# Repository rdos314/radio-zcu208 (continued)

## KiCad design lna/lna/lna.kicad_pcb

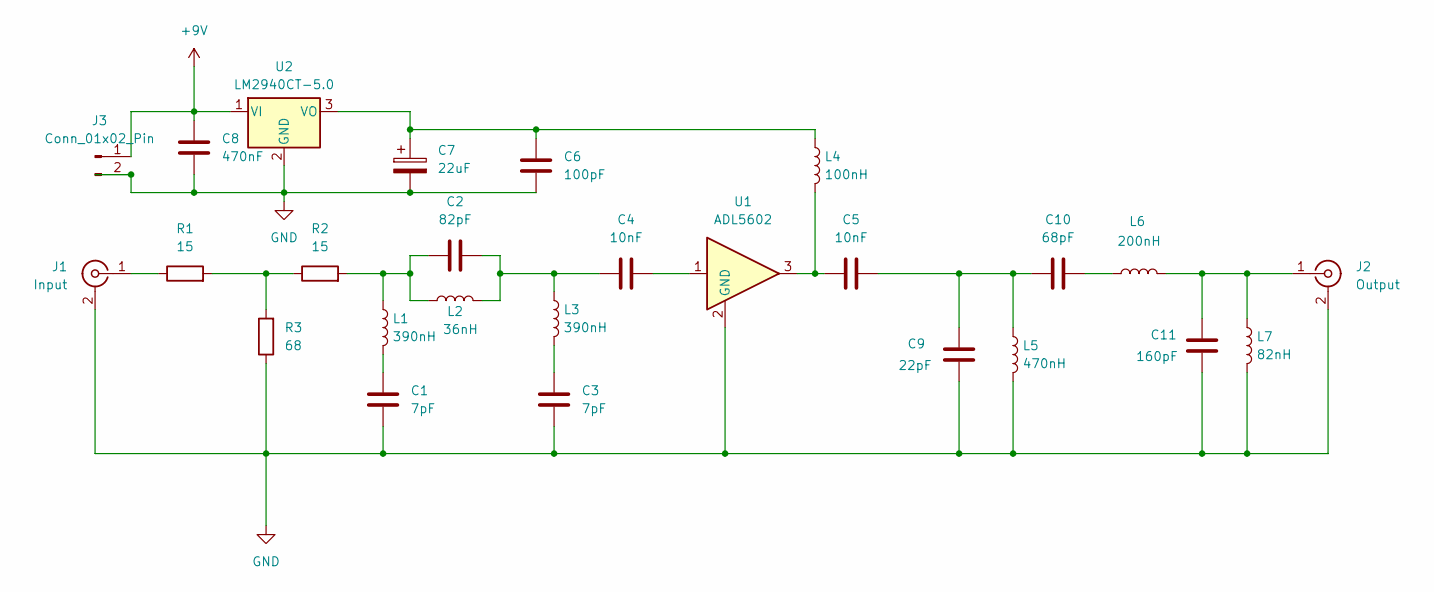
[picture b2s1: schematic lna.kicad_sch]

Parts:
C1, C3: 7pF; C_0402_1005Metric_Pad0.74x0.62mm_HandSolder
C2: 82pF; C_0402_1005Metric_Pad0.74x0.62mm_HandSolder
C4, C5: 10nF; C_0402_1005Metric_Pad0.74x0.62mm_HandSolder
C6: 100pF; C_0805_2012Metric_Pad1.18x1.45mm_HandSolder
C7: 22uF; CP_Radial_D6.3mm_P2.50mm
C8: 470nF; C_Radial_D10.0mm_H12.5mm_P5.00mm
C9: 22pF; C_0402_1005Metric_Pad0.74x0.62mm_HandSolder
C10: 68pF; C_0402_1005Metric_Pad0.74x0.62mm_HandSolder
C11: 160pF; C_0402_1005Metric_Pad0.74x0.62mm_HandSolder
J1: Input; SMA_Amphenol_132289_EdgeMount
J2: Output; SMA_Amphenol_132289_EdgeMount
J3: Conn_01x02_Pin; PinHeader_1x02_P2.54mm_Vertical
L1, L3: 390nH; L_0402_1005Metric_Pad0.77x0.64mm_HandSolder
L2: 36nH; L_0402_1005Metric_Pad0.77x0.64mm_HandSolder
L4: 100nH; L_0805_2012Metric_Pad1.05x1.20mm_HandSolder
L5: 470nH; L_0402_1005Metric_Pad0.77x0.64mm_HandSolder
L6: 200nH; L_0402_1005Metric_Pad0.77x0.64mm_HandSolder
L7: 82nH; L_0402_1005Metric_Pad0.77x0.64mm_HandSolder
R1, R2: 15; R_0402_1005Metric_Pad0.72x0.64mm_HandSolder
R3: 68; R_0402_1005Metric_Pad0.72x0.64mm_HandSolder
U1: ADL5602; SOT-89-3_Handsoldering
U2: LM2940CT-5.0; TO-220-3_Horizontal_TabDown

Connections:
+9V: C8.1, J3.1, U2.1 (VI)
GND: C1.2, C3.2, C6.2, C7.2, C8.2, C9.2, C11.2, J1.2 (Ext), J2.2 (Ext), J3.2, L5.2, L7.2, R3.1, U1.2 (GND_2), U2.2 (GND)
unnamed: C1.1, L1.2
unnamed: C2.1, L1.1, L2.1, R2.2
unnamed: C2.2, C4.1, L2.2, L3.1
unnamed: C3.1, L3.2
unnamed: C4.2, U1.1
unnamed: C5.1, L4.2, U1.3
unnamed: C5.2, C9.1, C10.1, L5.1
unnamed: C10.2, L6.1
unnamed: J1.1 (In), R1.1
unnamed: C11.1, J2.1 (In), L6.2, L7.1
unnamed: R1.2, R2.1, R3.2
unnamed: C6.1, C7.1, L4.1, U2.3 (VO)

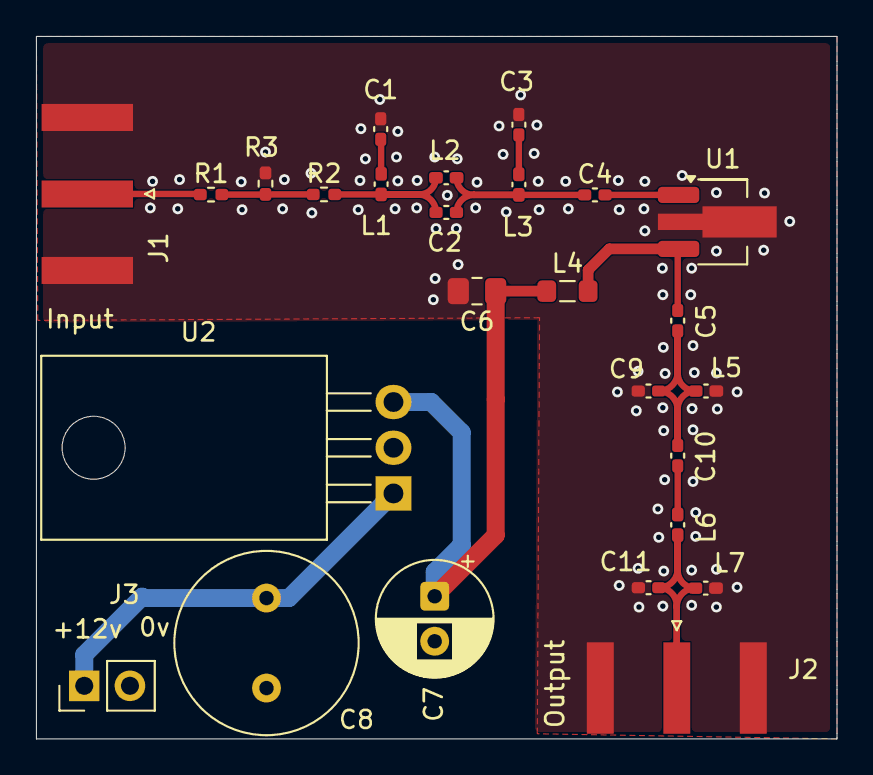
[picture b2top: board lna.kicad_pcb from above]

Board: 4 copper layers, 44.5 x 39.0 mm, 26 parts (0 on the bottom side), 14 nets.

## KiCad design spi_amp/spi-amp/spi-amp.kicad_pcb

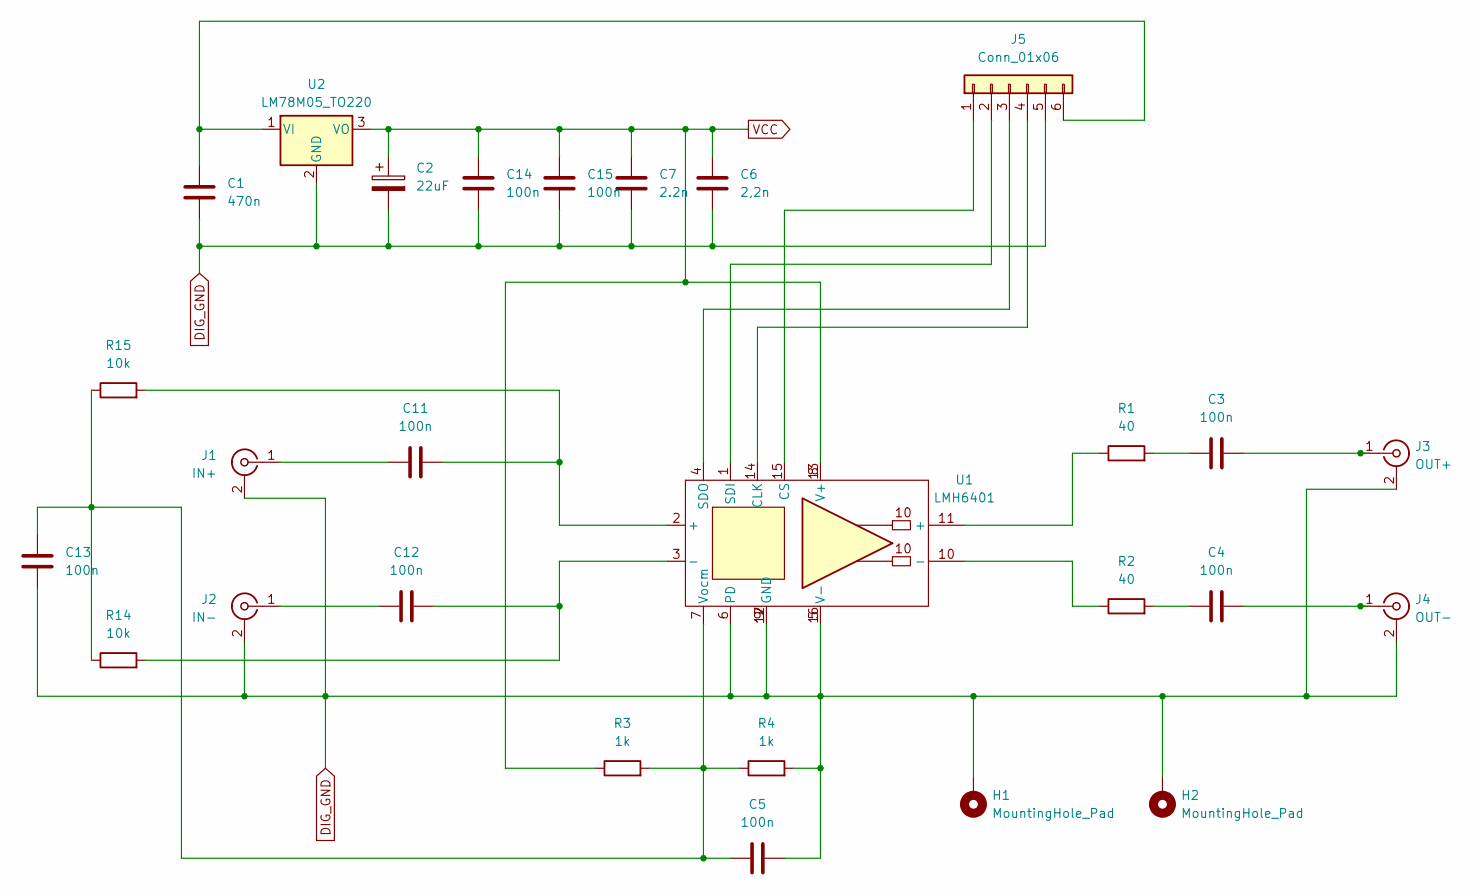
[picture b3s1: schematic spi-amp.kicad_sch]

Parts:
C1: 470n; C_Disc_D4.3mm_W1.9mm_P5.00mm
C2: 22uF; CP_Radial_D6.3mm_P2.50mm
C3, C4, C11, C12: 100n; C_0402_1005Metric_Pad0.74x0.62mm_HandSolder
C5, C13, C14, C15: 100n; C_0805_2012Metric_Pad1.18x1.45mm_HandSolder
C6: 2,2n; C_0402_1005Metric_Pad0.74x0.62mm_HandSolder
C7: 2.2n; C_0402_1005Metric_Pad0.74x0.62mm_HandSolder
H1, H2: MountingHole_Pad; MountingHole_3.2mm_M3_Pad
J1: IN+; SMA_Amphenol_132289_EdgeMount
J2: IN-; SMA_Amphenol_132289_EdgeMount
J3: OUT+; SMA_Amphenol_132289_EdgeMount
J4: OUT-; SMA_Amphenol_132289_EdgeMount
J5: Conn_01x06; PinSocket_1x06_P2.54mm_Horizontal
R1, R2: 40; R_0402_1005Metric_Pad0.72x0.64mm_HandSolder
R3, R4: 1k; R_0805_2012Metric_Pad1.20x1.40mm_HandSolder
R14, R15: 10k; R_0402_1005Metric_Pad0.72x0.64mm_HandSolder
U1: LMH6401; UQFN-16-custom
U2: LM78M05_TO220; TO-220-3_Horizontal_TabDown

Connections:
DIG_GND: C1.2, C2.2, C5.2, C6.1, C7.1, C13.1, C14.1, C15.1, H1.1 (1_1), H2.1 (1_1), J1.2 (Ext), J2.2 (Ext), J3.2 (Ext), J4.2 (Ext), J5.5, R4.2, U1.5 (V-), U1.6 (PD), U1.9 (GND), U1.12 (GND), U1.16 (V-), U1.17 (GND), U2.2 (GND)
unnamed: C3.1, R1.2
unnamed: C4.1, R2.2
unnamed: C11.2, R15.2, U1.2 (+)
unnamed: C12.2, R14.2, U1.3 (-)
unnamed: C11.1, J1.1 (In)
unnamed: C12.1, J2.1 (In)
unnamed: C3.2, J3.1 (In)
unnamed: C4.2, J4.1 (In)
unnamed: J5.1, U1.15 (CS)
unnamed: J5.2, U1.1 (SDI)
unnamed: J5.3, U1.4 (SDO)
unnamed: J5.4, U1.14 (CLK)
unnamed: C1.1, J5.6, U2.1 (VI)
unnamed: R1.1, U1.11 (+)
unnamed: R2.1, U1.10 (-)
unnamed: C5.1, C13.2, R3.2, R4.1, R14.1, R15.1, U1.7 (Vocm)
VCC: C2.1, C6.2, C7.2, C14.2, C15.2, R3.1, U1.8 (V+), U1.13 (V+), U2.3 (VO)

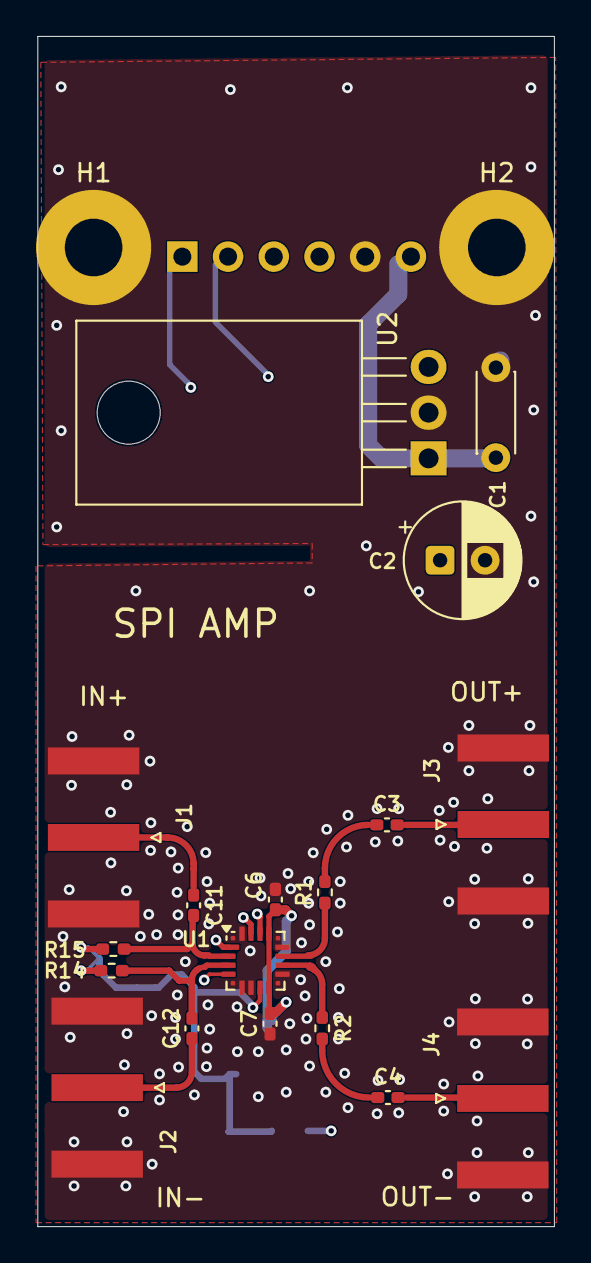
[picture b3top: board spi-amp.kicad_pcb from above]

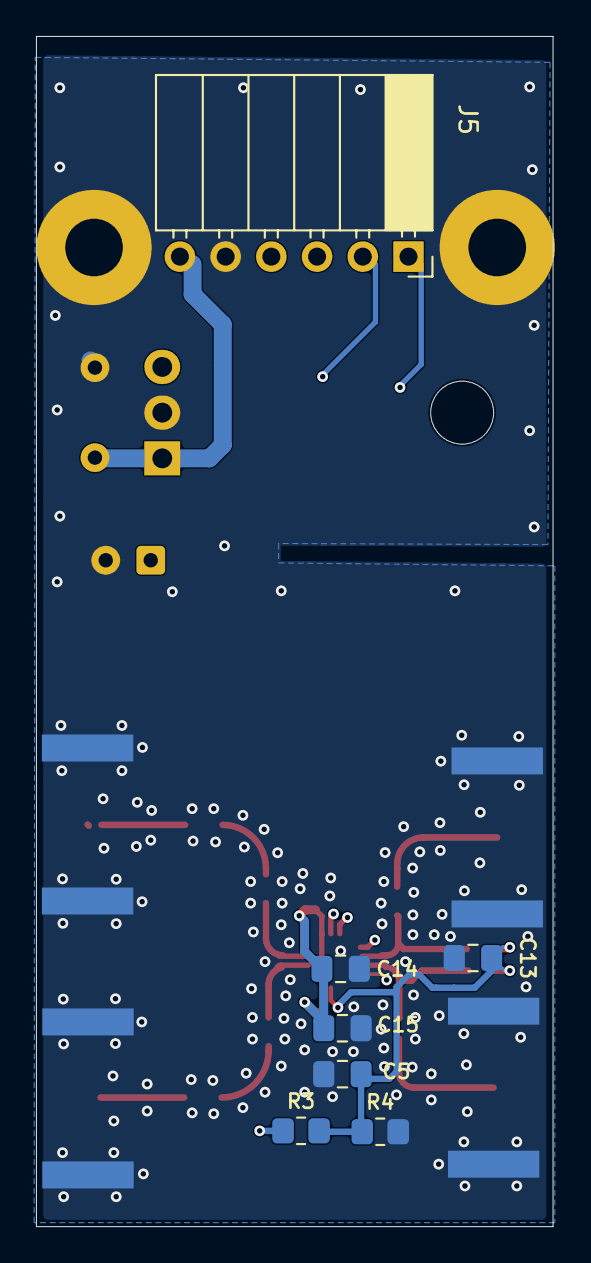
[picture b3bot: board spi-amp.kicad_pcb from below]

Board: 4 copper layers, 28.7 x 66.1 mm, 27 parts (7 on the bottom side), 18 nets.

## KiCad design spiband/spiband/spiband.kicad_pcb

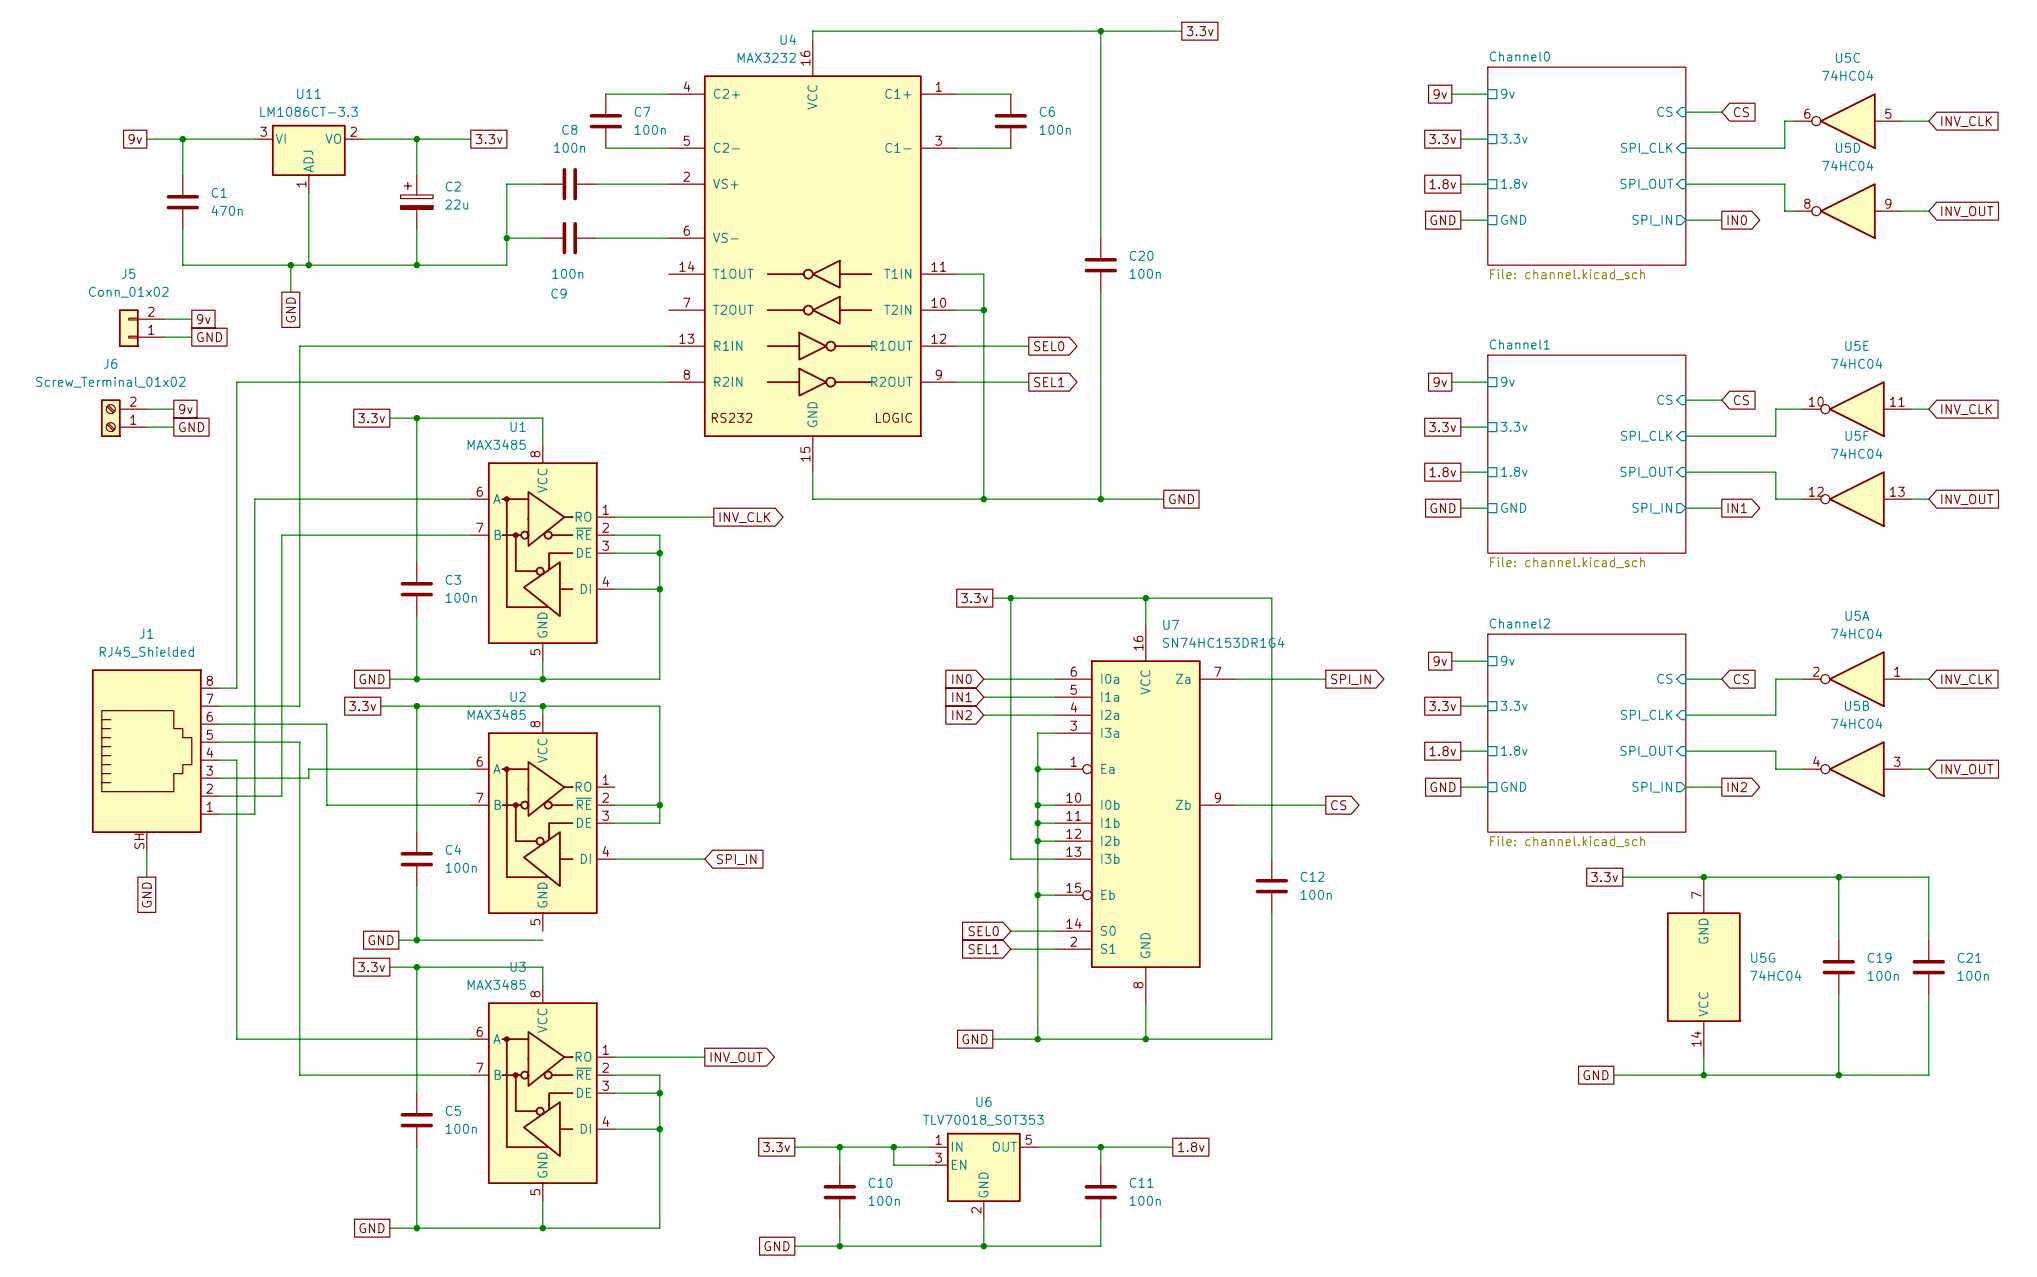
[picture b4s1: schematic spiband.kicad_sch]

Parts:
C1: 470n; C_0805_2012Metric_Pad1.18x1.45mm_HandSolder
C2: 22u; CP_Radial_D6.3mm_P2.50mm
C3, C4, C5, C6, C7, C8, C9, C11, C12, C19, C20, C21: 100n; C_0805_2012Metric_Pad1.18x1.45mm_HandSolder
C10: 100n; C_Disc_D4.3mm_W1.9mm_P5.00mm
J1: RJ45_Shielded; RJ45
J5: Conn_01x02; PinHeader_1x02_P2.54mm_Vertical
J6: Screw_Terminal_01x02; TerminalBlock_Phoenix_MKDS-1,5-2_1x02_P5.00mm_Horizontal
U1, U2, U3: MAX3485; SOIC-8_3.9x4.9mm_P1.27mm
U4: MAX3232; SSOP-16_5.3x6.2mm_P0.65mm
U5: 74HC04; SOIC-14_3.9x8.7mm_P1.27mm
U6: TLV70018_SOT353; SOT-353_SC-70-5
U7: SN74HC153DR1G4; SOIC-16_3.9x9.9mm_P1.27mm
U11: LM1086CT-3.3; TO-220-3_Horizontal_TabDown

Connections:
1.8v: C11.1, U6.5 (OUT); also elsewhere on the board
3.3v: C2.1, C3.1, C4.1, C5.1, C10.1, C12.1, C19.1, C20.1, C21.1, U1.8 (VCC), U2.2 (~RE), U2.3 (DE), U2.8 (VCC), U3.8 (VCC), U4.16 (VCC), U5.7 (GND), U6.1 (IN), U6.3 (EN), U7.13 (I3b), U7.16 (VCC), U11.2 (VO); also elsewhere on the board
9v: C1.1, J5.2, J6.2, U11.3 (VI); also elsewhere on the board
/Channel0/SPI_CLK: U5.6; also elsewhere on the board
/Channel0/SPI_OUT: U5.8; also elsewhere on the board
/Channel1/SPI_CLK: U5.10; also elsewhere on the board
/Channel1/SPI_OUT: U5.12; also elsewhere on the board
/Channel2/SPI_CLK: U5.2; also elsewhere on the board
/Channel2/SPI_OUT: U5.4; also elsewhere on the board
CS: U7.9 (Zb); also elsewhere on the board
GND: C1.2, C2.2, C3.2, C4.2, C5.2, C8.1, C9.1, C10.2, C11.2, C12.2, C19.2, C20.2, C21.2, J1.SH, J5.1, J6.1, U1.2 (~RE), U1.3 (DE), U1.4 (DI), U1.5 (GND), U3.2 (~RE), U3.3 (DE), U3.4 (DI), U3.5 (GND), U4.10 (T2IN), U4.11 (T1IN), U4.15 (GND), U5.14 (VCC), U6.2 (GND), U7.1 (Ea), U7.3 (I3a), U7.8 (GND), U7.10 (I0b), U7.11 (I1b), U7.12 (I2b), U7.15 (Eb), U11.1 (ADJ); also elsewhere on the board
IN0: U7.6 (I0a); also elsewhere on the board
IN1: U7.5 (I1a); also elsewhere on the board
IN2: U7.4 (I2a); also elsewhere on the board
INV_CLK: U1.1 (RO), U5.1, U5.5, U5.11
INV_OUT: U3.1 (RO), U5.3, U5.9, U5.13
unnamed: J1.1, U1.6 (A)
unnamed: J1.2, U1.7 (B)
unnamed: J1.3, U2.6 (A)
unnamed: J1.6, U2.7 (B)
unnamed: J1.4, U3.6 (A)
unnamed: J1.5, U3.7 (B)
unnamed: C6.1, U4.1 (C1+)
unnamed: C6.2, U4.3 (C1-)
unnamed: C7.1, U4.4 (C2+)
unnamed: C7.2, U4.5 (C2-)
unnamed: J1.7, U4.13 (R1IN)
unnamed: J1.8, U4.8 (R2IN)
unnamed: C8.2, U4.2 (VS+)
unnamed: C9.2, U4.6 (VS-)
SEL0: U4.12 (R1OUT), U7.14 (S0)
SEL1: U4.9 (R2OUT), U7.2 (S1)
SPI_IN: U2.4 (DI), U7.7 (Za)

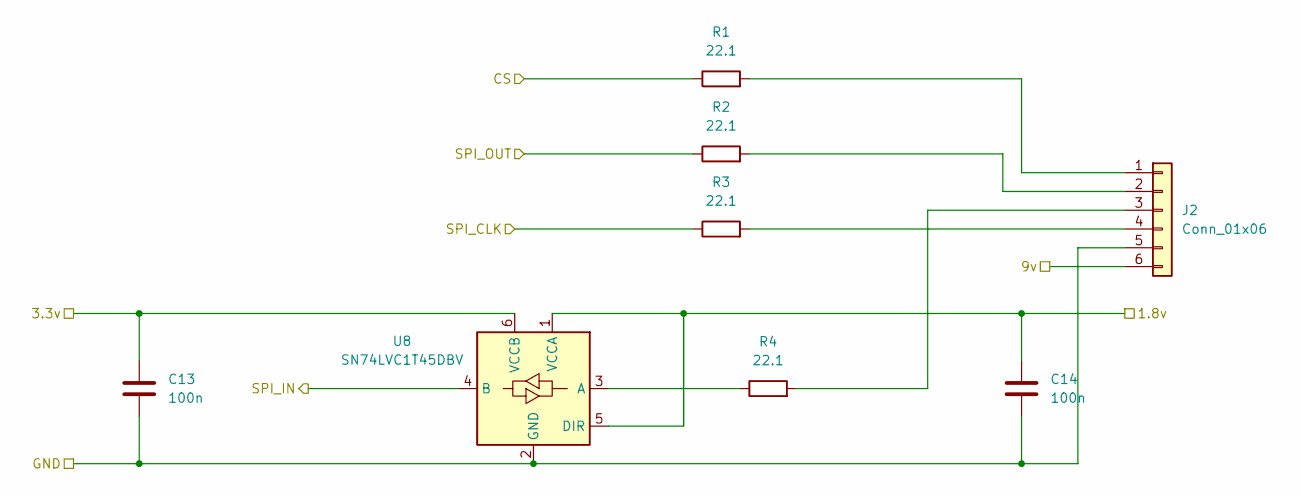
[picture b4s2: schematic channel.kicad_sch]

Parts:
C13, C14: 100n; C_0805_2012Metric_Pad1.18x1.45mm_HandSolder
J2: Conn_01x06; PinSocket_1x06_P2.54mm_Vertical
R1, R2, R3, R4: 22.1; R_0805_2012Metric_Pad1.20x1.40mm_HandSolder
U8: SN74LVC1T45DBV; SOT-23-6

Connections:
1.8v: C14.1, U8.1 (VCCA), U8.5 (DIR); also elsewhere on the board
3.3v: C13.1, U8.6 (VCCB); also elsewhere on the board
9v: J2.6; also elsewhere on the board
/Channel0/SPI_CLK: R3.1; also elsewhere on the board
/Channel0/SPI_OUT: R2.1; also elsewhere on the board
CS: R1.1; also elsewhere on the board
GND: C13.2, C14.2, J2.5, U8.2 (GND); also elsewhere on the board
IN0: U8.4 (B); also elsewhere on the board
unnamed: J2.1, R1.2
unnamed: J2.2, R2.2
unnamed: J2.3, R4.2
unnamed: J2.4, R3.2
unnamed: R4.1, U8.3 (A)

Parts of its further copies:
C15, C16, C17, C18: 100n; C_0805_2012Metric_Pad1.18x1.45mm_HandSolder
J3, J4: Conn_01x06; PinSocket_1x06_P2.54mm_Vertical
R5, R6, R7, R8, R9, R10, R11, R12: 22.1; R_0805_2012Metric_Pad1.20x1.40mm_HandSolder
U9, U10: SN74LVC1T45DBV; SOT-23-6

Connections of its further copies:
1.8v: C16.1, C18.1, U9.1 (VCCA), U9.5 (DIR), U10.1 (VCCA), U10.5 (DIR); also elsewhere on the board
3.3v: C15.1, C17.1, U9.6 (VCCB), U10.6 (VCCB); also elsewhere on the board
9v: J3.6, J4.6; also elsewhere on the board
/Channel1/SPI_CLK: R7.1; also elsewhere on the board
/Channel1/SPI_OUT: R6.1; also elsewhere on the board
/Channel2/SPI_CLK: R11.1; also elsewhere on the board
/Channel2/SPI_OUT: R10.1; also elsewhere on the board
CS: R5.1, R9.1; also elsewhere on the board
GND: C15.2, C16.2, C17.2, C18.2, J3.5, J4.5, U9.2 (GND), U10.2 (GND); also elsewhere on the board
IN1: U9.4 (B); also elsewhere on the board
IN2: U10.4 (B); also elsewhere on the board
unnamed: J3.1, R5.2
unnamed: J3.2, R6.2
unnamed: J3.3, R8.2
unnamed: J3.4, R7.2
unnamed: J4.1, R9.2
unnamed: J4.2, R10.2
unnamed: J4.3, R12.2
unnamed: J4.4, R11.2
unnamed: R8.1, U9.3 (A)
unnamed: R12.1, U10.3 (A)

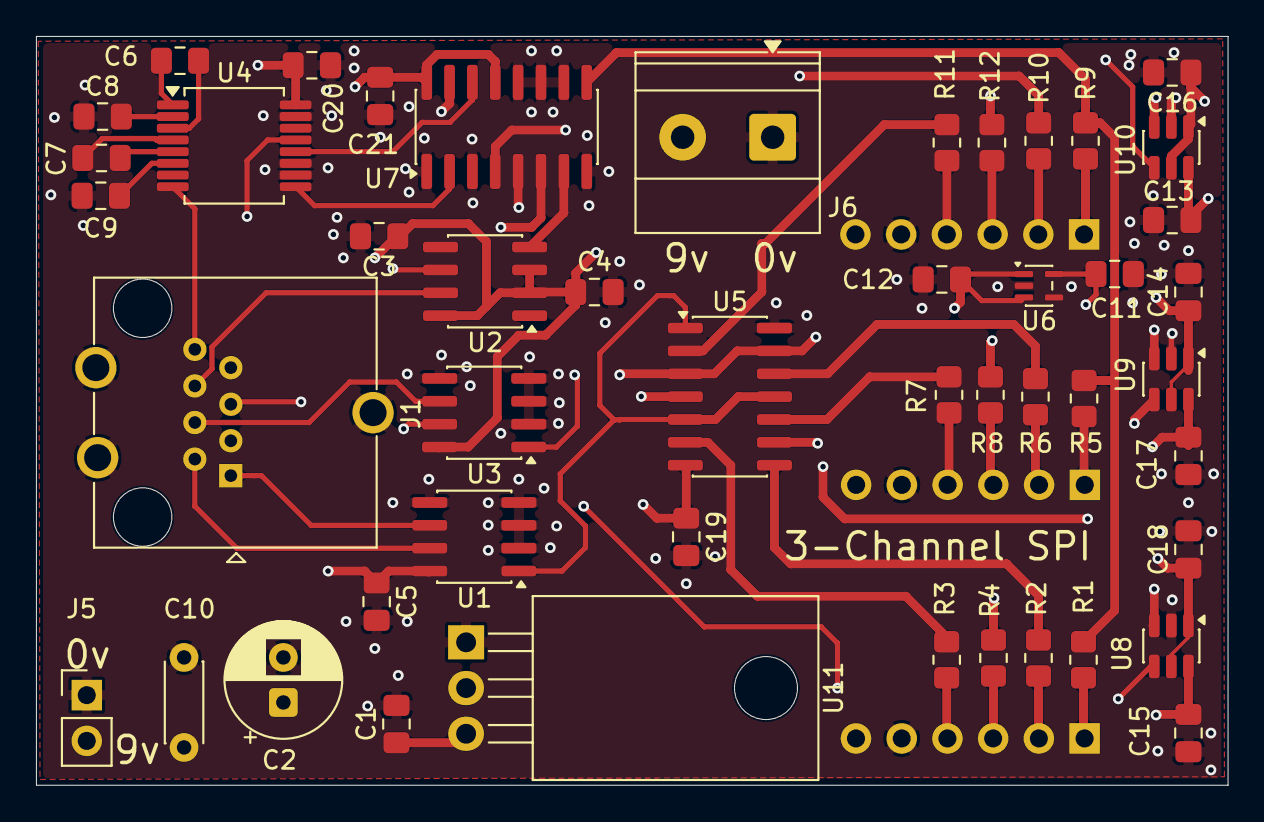
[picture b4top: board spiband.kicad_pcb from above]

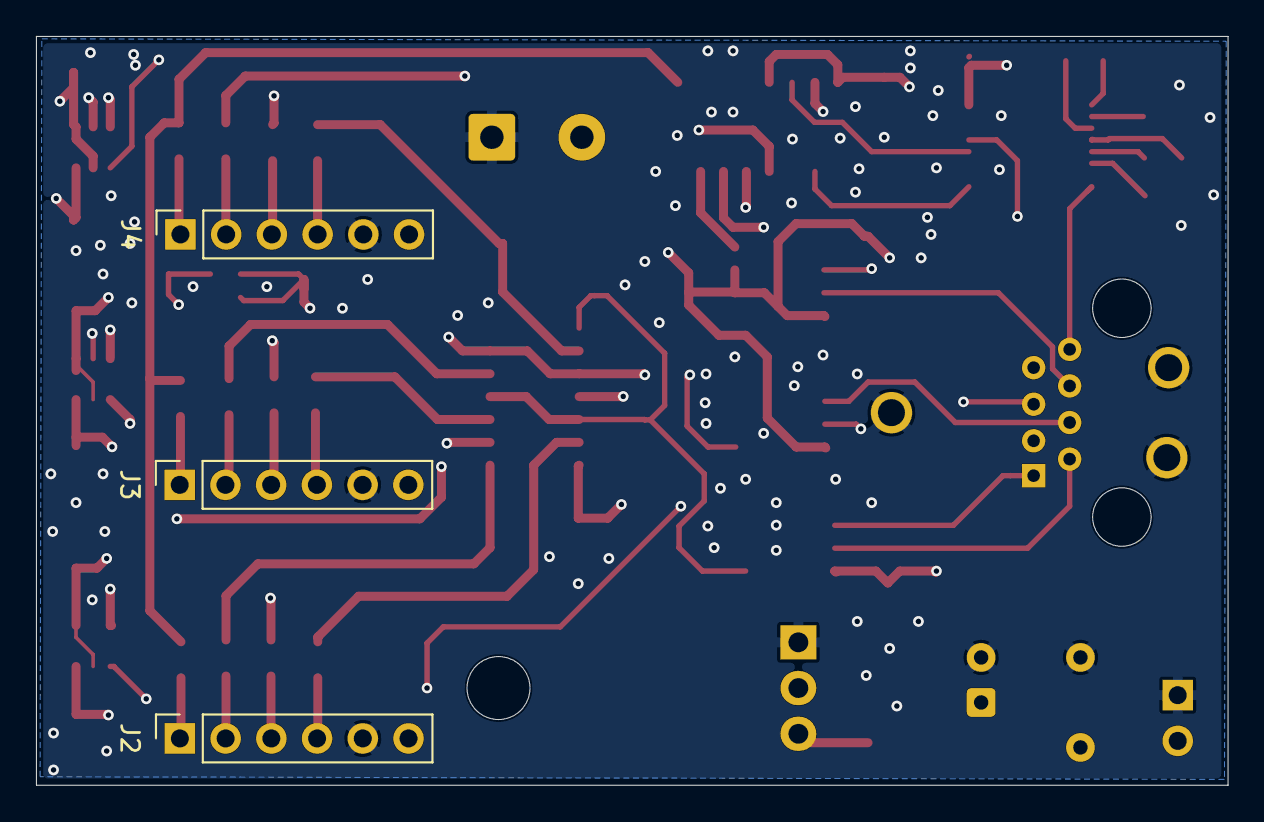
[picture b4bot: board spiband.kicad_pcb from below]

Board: 4 copper layers, 66.2 x 41.6 mm, 50 parts (3 on the bottom side), 48 nets.

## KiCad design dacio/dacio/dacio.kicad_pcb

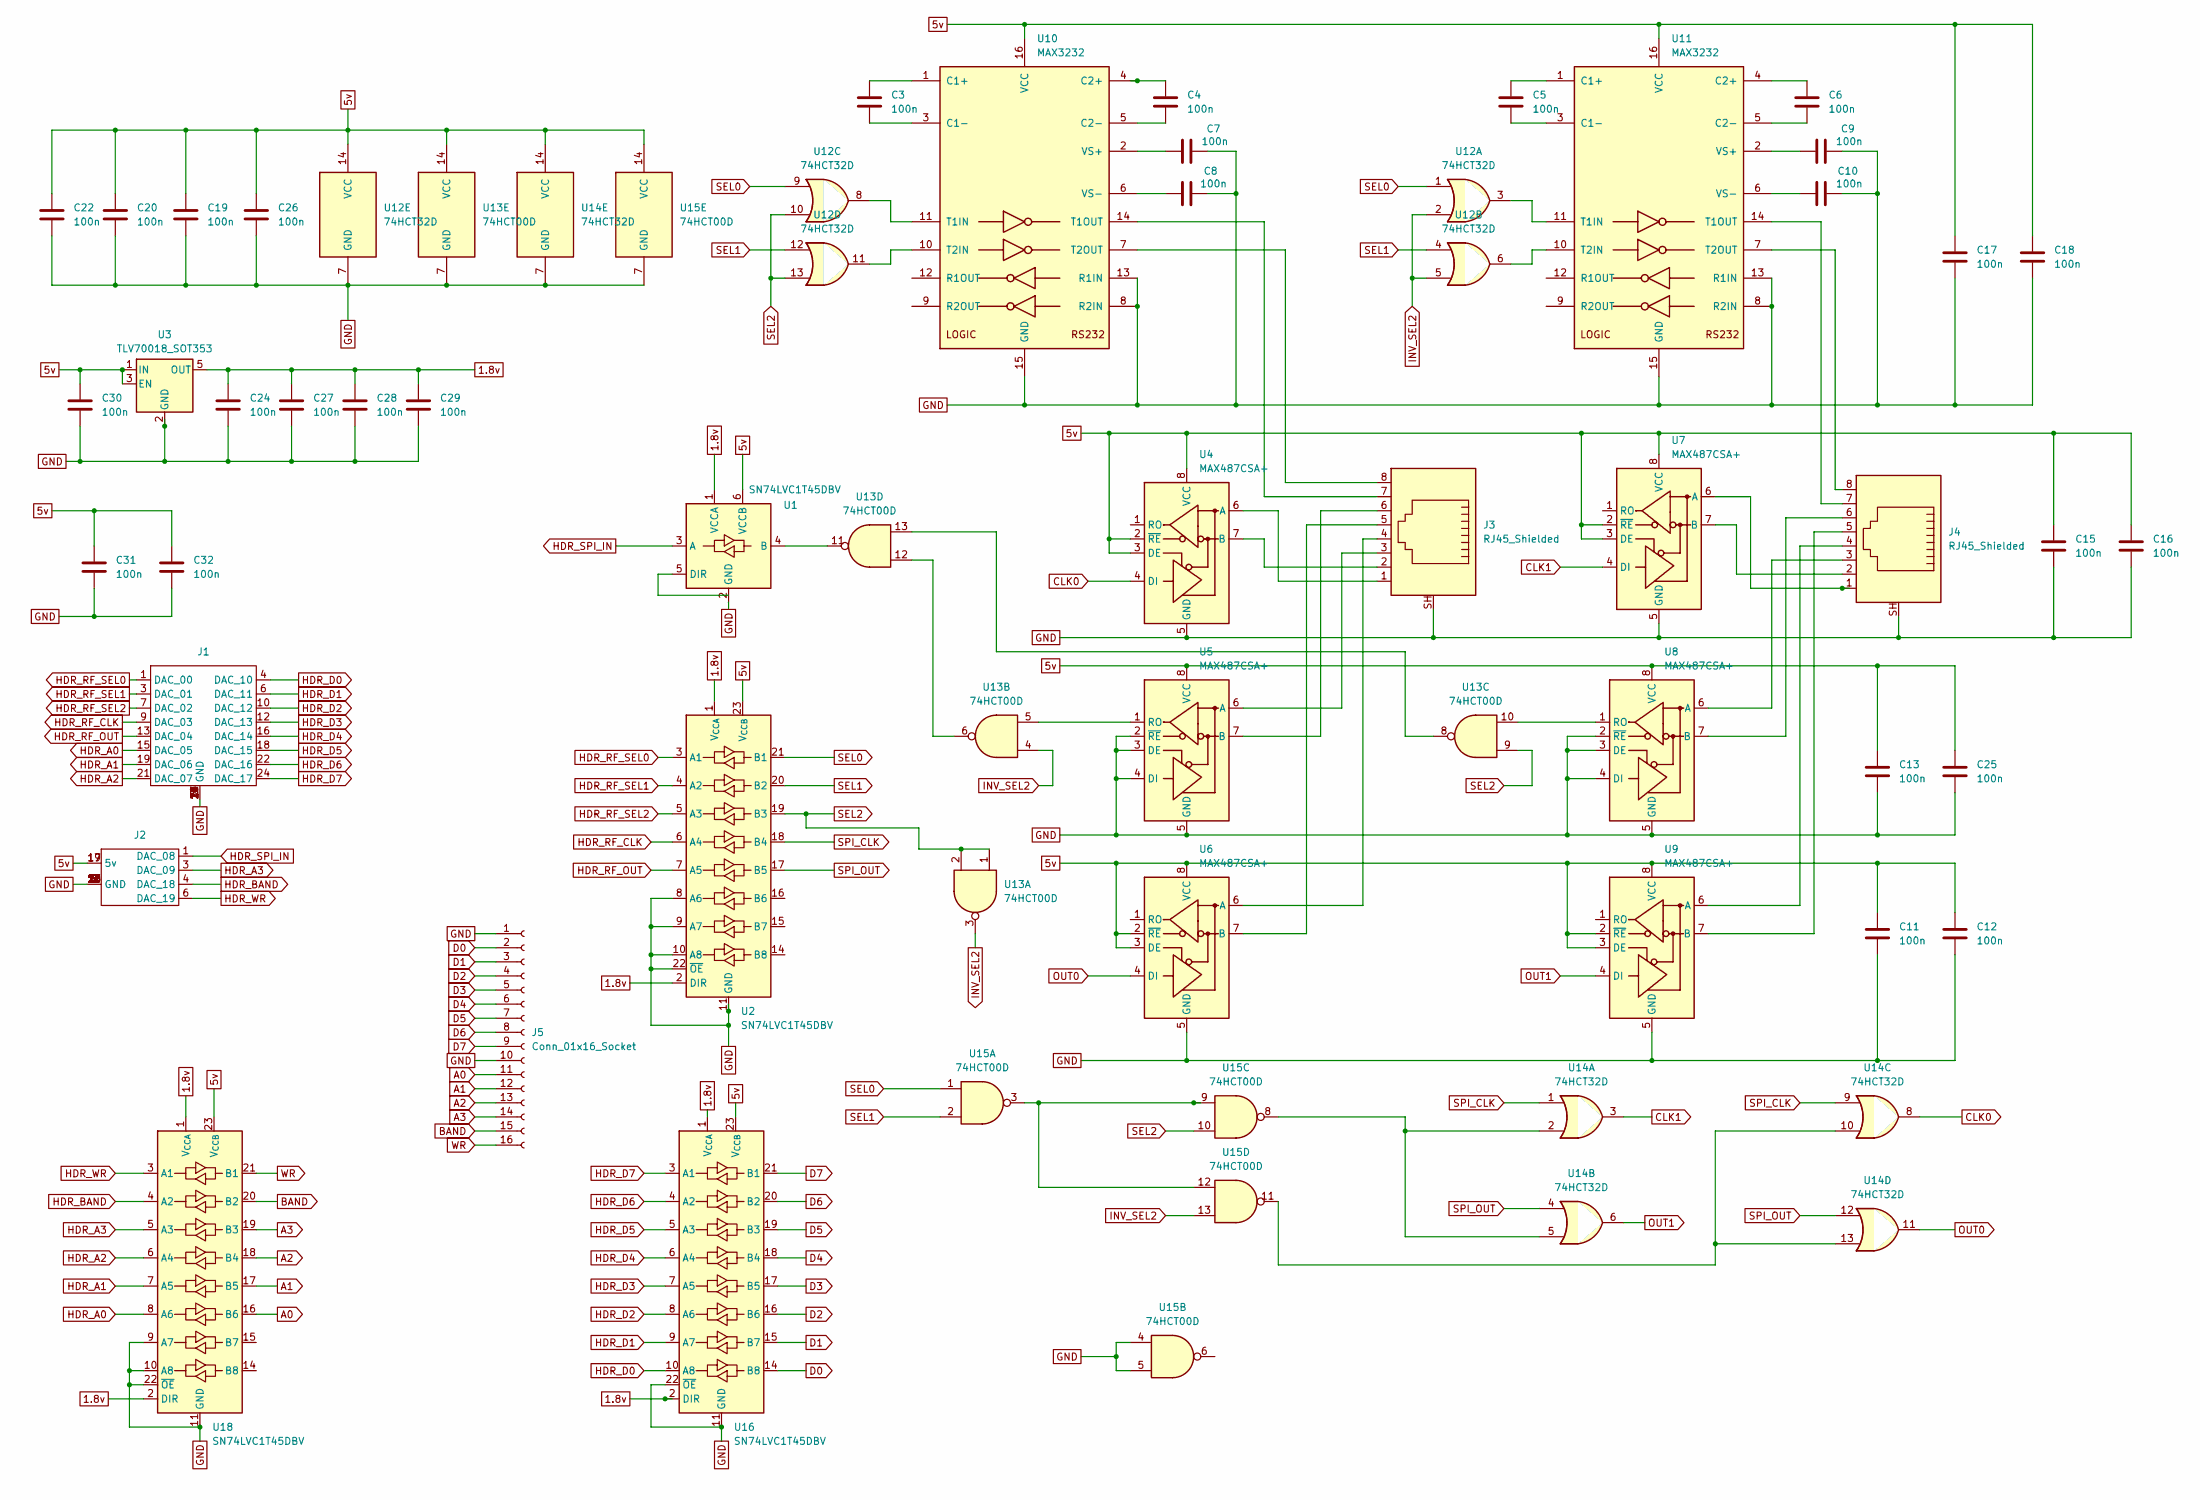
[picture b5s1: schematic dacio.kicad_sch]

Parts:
C3, C4, C5, C6, C7, C8, C9, C10, C11, C12, C13, C15, C16, C17, C18, C19, C20, C22, C24, C25, C26, C27, C28, C29, C30, C31, C32: 100n; C_0805_2012Metric_Pad1.18x1.45mm_HandSolder
J1, J2: PinSocket_2x12_P2.54mm_Vertical
J3, J4: RJ45_Shielded; RJ45
J5: Conn_01x16_Socket; PinHeader_1x16_P2.54mm_Vertical
U1: SN74LVC1T45DBV; SOT-23-6
U2, U16, U18: SN74LVC1T45DBV; TSSOP-24_4.4x7.8mm_P0.65mm
U3: TLV70018_SOT353; SOT-353_SC-70-5
U4, U5, U6, U7, U8, U9: MAX487CSA+; SOIC-8_3.9x4.9mm_P1.27mm
U10, U11: MAX3232; SSOP-16_5.3x6.2mm_P0.65mm
U12, U14: 74HCT32D; SOIC-14_3.9x8.7mm_P1.27mm
U13, U15: 74HCT00D; SOIC-14_3.9x8.7mm_P1.27mm

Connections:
1.8v: C24.1, C27.1, C28.1, C29.1, U1.1 (VCCA), U2.1 (V_{CCA}), U2.2 (DIR), U3.5 (OUT), U16.1 (V_{CCA}), U16.2 (DIR), U18.1 (V_{CCA}), U18.2 (DIR)
5v: C11.1, C12.1, C13.1, C15.1, C16.1, C17.1, C18.1, C19.1, C20.1, C22.1, C25.1, C26.1, C30.1, C31.1, C32.1, J2.17 (5v), J2.19 (5v), U1.6 (VCCB), U2.23 (V_{CCB}), U2.24 (V_{CCB}), U3.1 (IN), U3.3 (EN), U4.2 (~RE), U4.3 (DE), U4.8 (VCC), U5.8 (VCC), U6.2 (~RE), U6.3 (DE), U6.8 (VCC), U7.2 (~RE), U7.3 (DE), U7.8 (VCC), U8.8 (VCC), U9.2 (~RE), U9.3 (DE), U9.8 (VCC), U10.16 (VCC), U11.16 (VCC), U12.14 (VCC), U13.14 (VCC), U14.14 (VCC), U15.14 (VCC), U16.23 (V_{CCB}), U16.24 (V_{CCB}), U18.23 (V_{CCB}), U18.24 (V_{CCB})
A0: J5.11, U18.16 (B6)
A1: J5.12, U18.17 (B5)
A2: J5.13, U18.18 (B4)
A3: J5.14, U18.19 (B3)
BAND: J5.15, U18.20 (B2)
CLK0: U4.4 (DI), U14.8
CLK1: U7.4 (DI), U14.3
D0: J5.2, U16.14 (B8)
D1: J5.3, U16.15 (B7)
D2: J5.4, U16.16 (B6)
D3: J5.5, U16.17 (B5)
D4: J5.6, U16.18 (B4)
D5: J5.7, U16.19 (B3)
D6: J5.8, U16.20 (B2)
D7: J5.9, U16.21 (B1)
GND: C7.2, C8.2, C9.2, C10.2, C11.2, C12.2, C13.2, C15.2, C16.2, C17.2, C18.2, C19.2, C20.2, C22.2, C24.2, C25.2, C26.2, C27.2, C28.2, C29.2, C30.2, C31.2, C32.2, J1.2 (GND), J1.5 (GND), J1.8 (GND), J1.11 (GND), J1.14 (GND), J1.17 (GND), J1.20 (GND), J1.23 (GND), J2.2 (GND), J2.5 (GND), J2.7 (GND), J2.8 (GND), J2.10 (GND), J2.13 (GND), J2.15 (GND), J2.16 (GND), J2.18 (GND), J2.20 (GND), J2.21 (GND), J2.23 (GND), J3.SH, J4.SH, J5.1, J5.10, U1.2 (GND), U2.8 (A6), U2.9 (A7), U2.10 (A8), U2.11 (GND), U2.12 (GND), U2.13 (GND), U2.22 (~OE), U3.2 (GND), U4.5 (GND), U5.2 (~RE), U5.3 (DE), U5.4 (DI), U5.5 (GND), U6.5 (GND), U7.5 (GND), U8.2 (~RE), U8.3 (DE), U8.4 (DI), U8.5 (GND), U9.5 (GND), U10.8 (R2IN), U10.13 (R1IN), U10.15 (GND), U11.8 (R2IN), U11.13 (R1IN), U11.15 (GND), U12.7 (GND), U13.7 (GND), U14.7 (GND), U15.4, U15.5, U15.7 (GND), U16.11 (GND), U16.12 (GND), U16.13 (GND), U16.22 (~OE), U18.9 (A7), U18.10 (A8), U18.11 (GND), U18.12 (GND), U18.13 (GND), U18.22 (~OE)
HDR_A0: J1.15 (DAC_05), U18.8 (A6)
HDR_A1: J1.19 (DAC_06), U18.7 (A5)
HDR_A2: J1.21 (DAC_07), U18.6 (A4)
HDR_A3: J2.3 (DAC_09), U18.5 (A3)
HDR_BAND: J2.4 (DAC_18), U18.4 (A2)
HDR_D0: J1.4 (DAC_10), U16.10 (A8)
HDR_D1: J1.6 (DAC_11), U16.9 (A7)
HDR_D2: J1.10 (DAC_12), U16.8 (A6)
HDR_D3: J1.12 (DAC_13), U16.7 (A5)
HDR_D4: J1.16 (DAC_14), U16.6 (A4)
HDR_D5: J1.18 (DAC_15), U16.5 (A3)
HDR_D6: J1.22 (DAC_16), U16.4 (A2)
HDR_D7: J1.24 (DAC_17), U16.3 (A1)
HDR_RF_CLK: J1.9 (DAC_03), U2.6 (A4)
HDR_RF_OUT: J1.13 (DAC_04), U2.7 (A5)
HDR_RF_SEL0: J1.1 (DAC_00), U2.3 (A1)
HDR_RF_SEL1: J1.3 (DAC_01), U2.4 (A2)
HDR_RF_SEL2: J1.7 (DAC_02), U2.5 (A3)
HDR_SPI_IN: J2.1 (DAC_08), U1.3 (A)
HDR_WR: J2.6 (DAC_19), U18.3 (A1)
INV_SEL2: U12.2, U12.5, U13.3, U13.4, U15.13
unnamed: U1.4 (B), U13.11
unnamed: J3.1, U4.6 (A)
unnamed: J3.2, U4.7 (B)
unnamed: J3.3, U5.6 (A)
unnamed: J3.6, U5.7 (B)
unnamed: U5.1 (RO), U13.5
unnamed: J3.4, U6.6 (A)
unnamed: J3.5, U6.7 (B)
unnamed: J4.1, U7.6 (A)
unnamed: J4.2, U7.7 (B)
unnamed: J4.3, U8.6 (A)
unnamed: J4.6, U8.7 (B)
unnamed: U8.1 (RO), U13.10
unnamed: J4.4, U9.6 (A)
unnamed: J4.5, U9.7 (B)
unnamed: C3.1, U10.1 (C1+)
unnamed: C3.2, U10.3 (C1-)
unnamed: C4.1, U10.4 (C2+)
unnamed: C4.2, U10.5 (C2-)
unnamed: U10.11 (T1IN), U12.8
unnamed: J3.7, U10.14 (T1OUT)
unnamed: U10.10 (T2IN), U12.11
unnamed: J3.8, U10.7 (T2OUT)
unnamed: C7.1, U10.2 (VS+)
unnamed: C8.1, U10.6 (VS-)
unnamed: C5.1, U11.1 (C1+)
unnamed: C5.2, U11.3 (C1-)
unnamed: C6.1, U11.4 (C2+)
unnamed: C6.2, U11.5 (C2-)
unnamed: U11.11 (T1IN), U12.3
unnamed: J4.7, U11.14 (T1OUT)
unnamed: U11.10 (T2IN), U12.6
unnamed: J4.8, U11.7 (T2OUT)
unnamed: C9.1, U11.2 (VS+)
unnamed: C10.1, U11.6 (VS-)
unnamed: U13.6, U13.12
unnamed: U13.8, U13.13
unnamed: U14.2, U14.5, U15.8
unnamed: U14.10, U14.13, U15.11
unnamed: U15.3, U15.9, U15.12
OUT0: U6.4 (DI), U14.11
OUT1: U9.4 (DI), U14.6
SEL0: U2.21 (B1), U12.1, U12.9, U15.1
SEL1: U2.20 (B2), U12.4, U12.12, U15.2
SEL2: U2.19 (B3), U12.10, U12.13, U13.1, U13.2, U13.9, U15.10
SPI_CLK: U2.18 (B4), U14.1, U14.9
SPI_OUT: U2.17 (B5), U14.4, U14.12
WR: J5.16, U18.21 (B1)

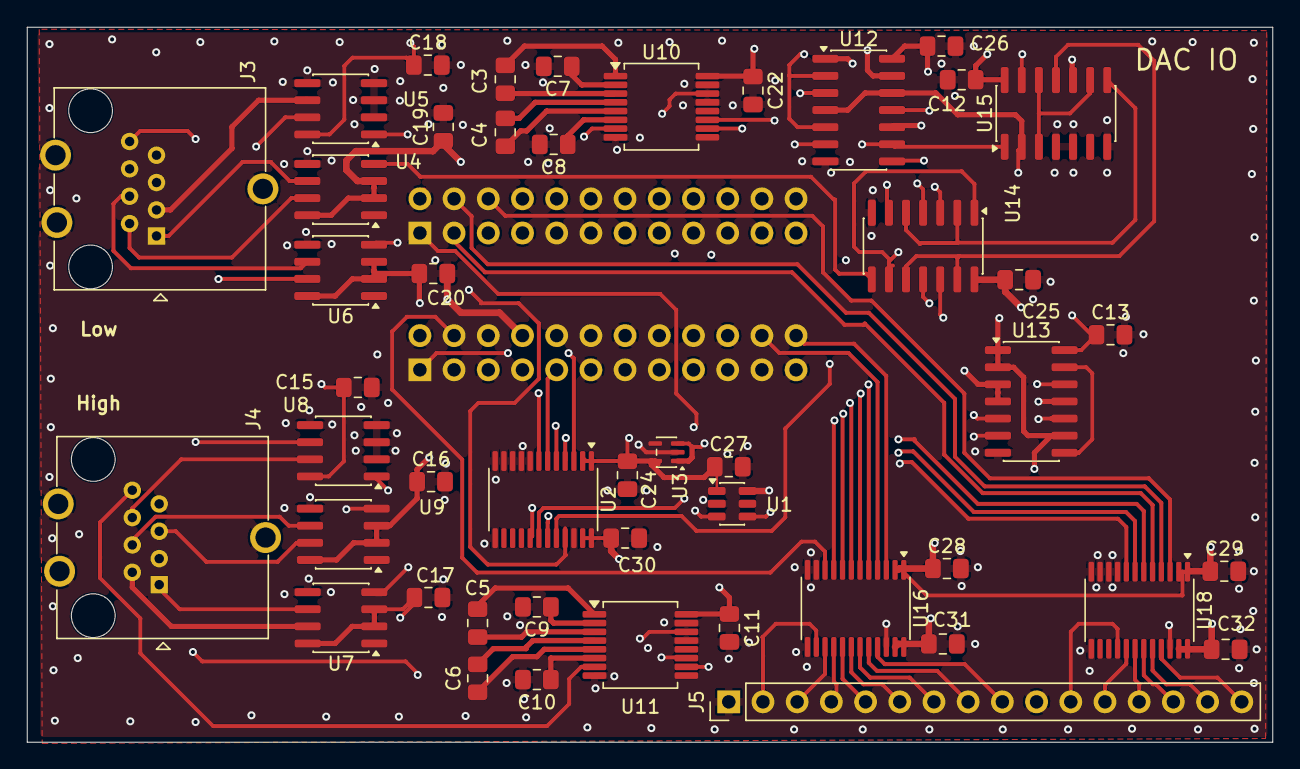
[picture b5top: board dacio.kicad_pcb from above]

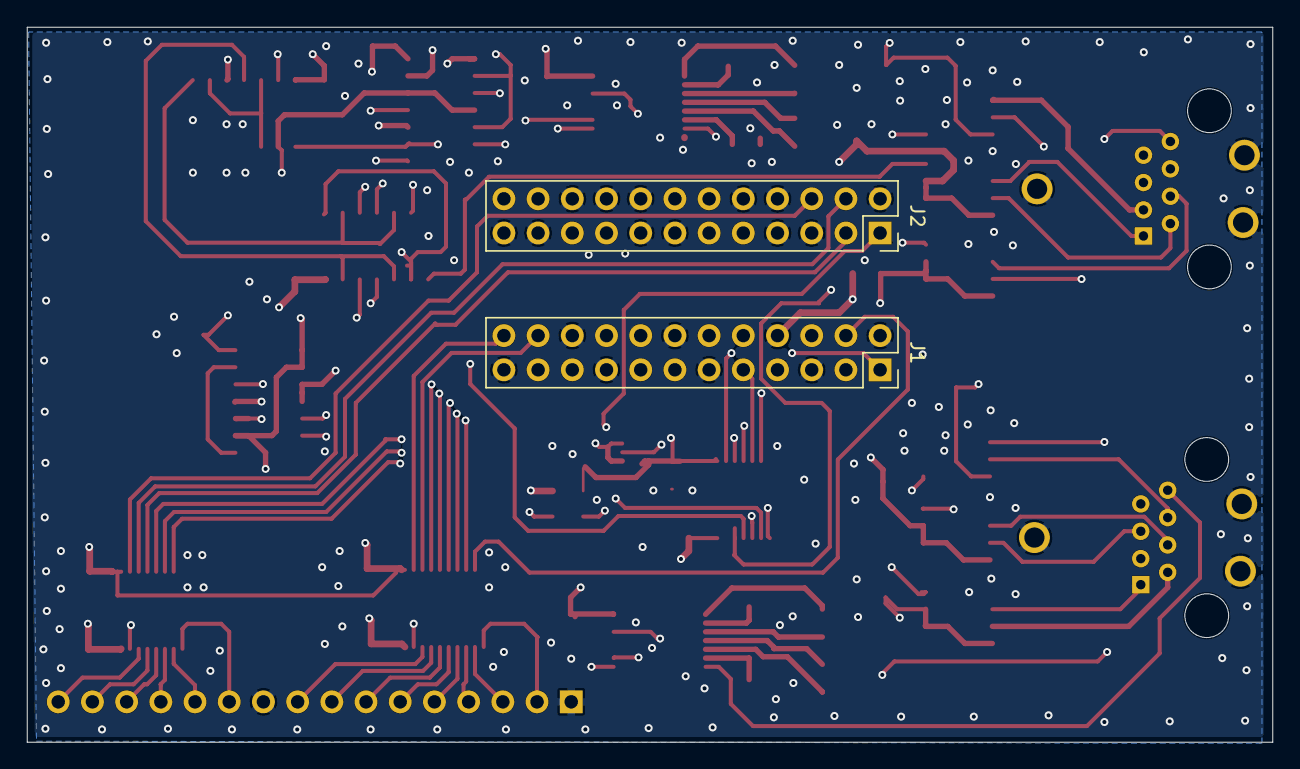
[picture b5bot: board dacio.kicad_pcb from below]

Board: 4 copper layers, 92.5 x 53.1 mm, 49 parts (2 on the bottom side), 87 nets.
